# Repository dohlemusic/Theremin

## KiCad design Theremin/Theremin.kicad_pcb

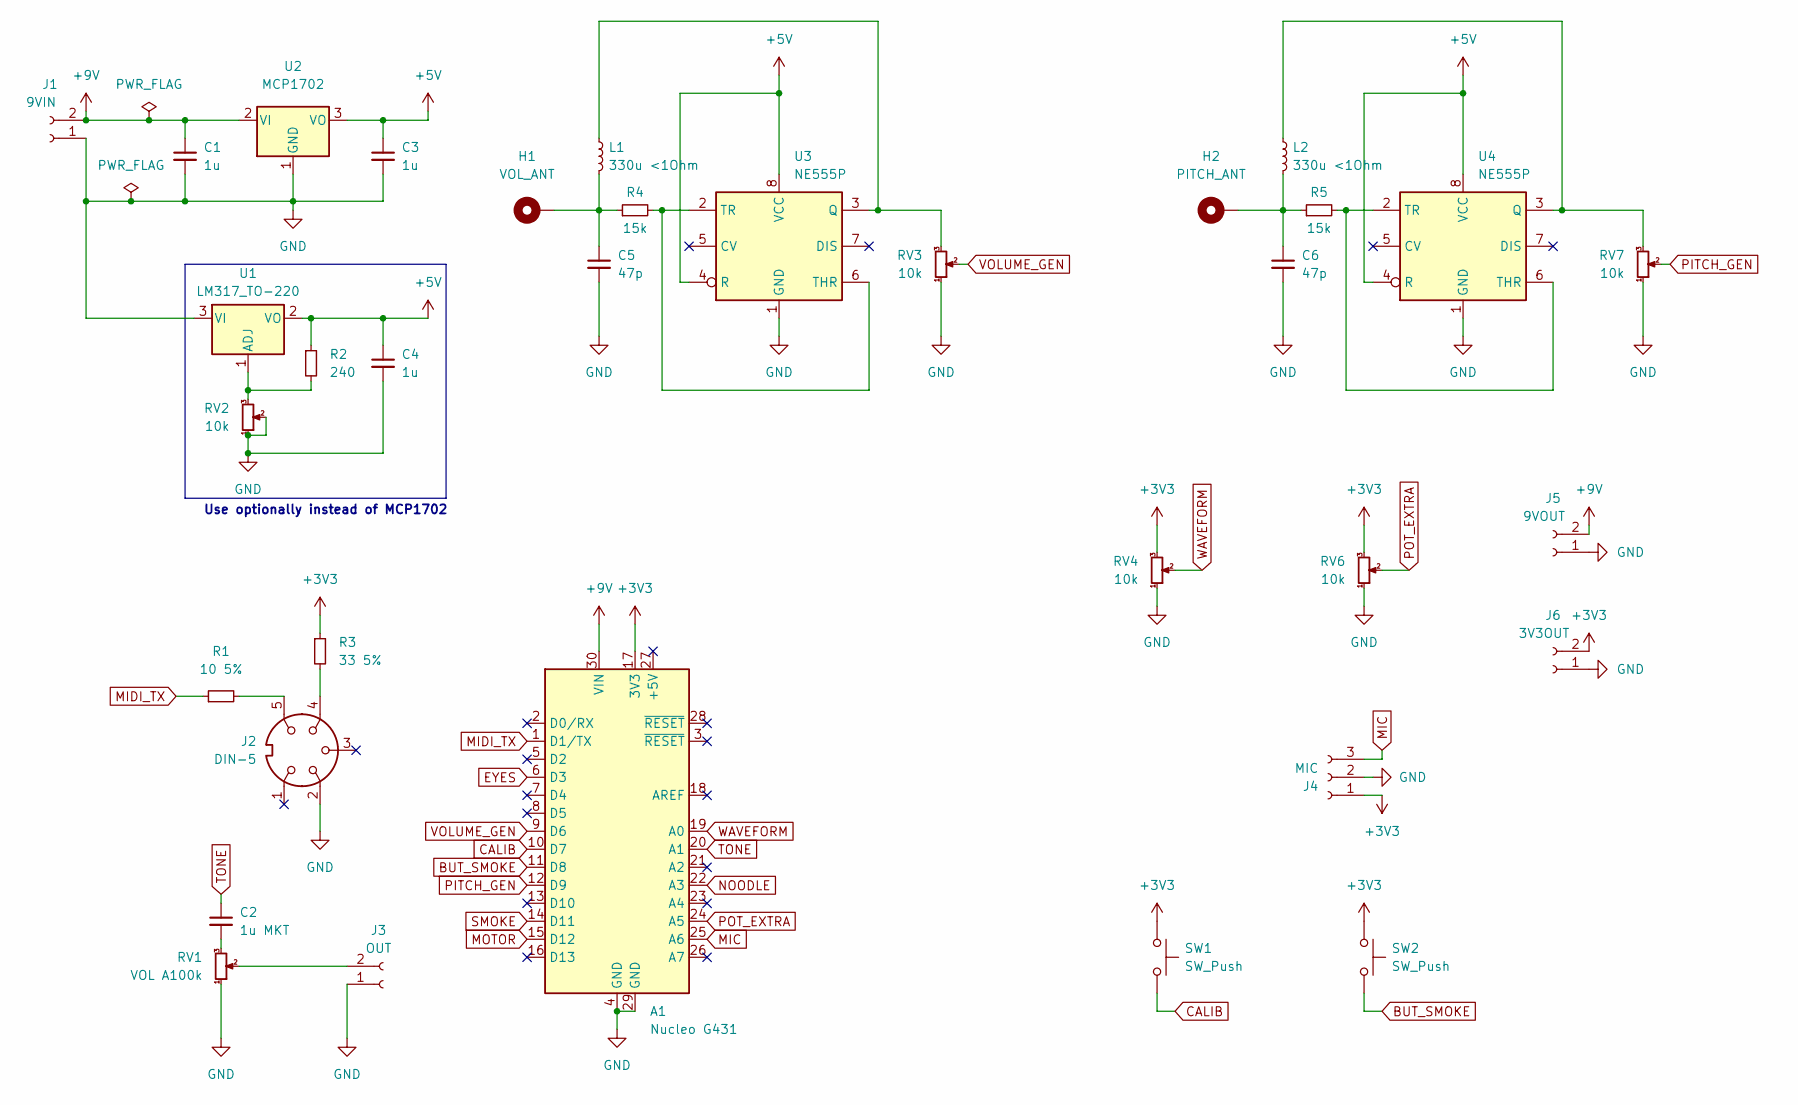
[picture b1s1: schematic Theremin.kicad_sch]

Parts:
A1: Nucleo G431; Arduino_Nano
C1, C3, C4: 1u; C_Rect_L7.0mm_W4.5mm_P5.00mm
C2: 1u MKT; C_Rect_L7.0mm_W4.5mm_P5.00mm
C5, C6: 47p; C_Disc_D3.0mm_W1.6mm_P2.50mm
H1: VOL_ANT; Pin_D1.0mm_L10.0mm
H2: PITCH_ANT; Pin_D1.0mm_L10.0mm
J1: 9VIN; JST_PH_B2B-PH-K_1x02_P2.00mm_Vertical
J2: DIN-5; MIDI_DIN5
J3: OUT; JST_PH_B2B-PH-K_1x02_P2.00mm_Vertical
J4: MIC; JST_PH_B3B-PH-K_1x03_P2.00mm_Vertical
J5: 9VOUT; JST_PH_B2B-PH-K_1x02_P2.00mm_Vertical
J6: 3V3OUT; JST_PH_B2B-PH-K_1x02_P2.00mm_Vertical
L1, L2: 330u <1Ohm; L_Radial_D7.5mm_P5.00mm_Fastron_07P
R1: 10 5%; R_Axial_DIN0207_L6.3mm_D2.5mm_P10.16mm_Horizontal
R2: 240; R_Axial_DIN0207_L6.3mm_D2.5mm_P10.16mm_Horizontal
R3: 33 5%; R_Axial_DIN0207_L6.3mm_D2.5mm_P10.16mm_Horizontal
R4, R5: 15k; R_Axial_DIN0207_L6.3mm_D2.5mm_P10.16mm_Horizontal
RV1: VOL A100k; JST_PH_B3B-PH-K_1x03_P2.00mm_Vertical
RV2, RV3, RV7: 10k; Potentiometer_Bourns_3299W_Vertical
RV4, RV6: 10k; JST_PH_B3B-PH-K_1x03_P2.00mm_Vertical
SW1, SW2: SW_Push; JST_PH_B2B-PH-K_1x02_P2.00mm_Vertical
U1: LM317_TO-220; TO-220-3_Vertical
U2: MCP1702; TO-92_Inline
U3, U4: NE555P; DIP-8_W7.62mm

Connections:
+3V3: A1.17 (3V3), J4.1, J6.2, R3.1, RV4.3, RV6.3, SW1.1, SW2.1
+5V: C3.1, C4.1, R2.1, U1.2 (VO), U2.3 (VO), U3.4 (R), U3.8 (VCC), U4.4 (R), U4.8 (VCC)
+9V: A1.30 (VIN), C1.1, J1.2, J5.2, U2.2 (VI)
BUT_SMOKE: A1.11 (D8), SW2.2
CALIB: A1.10 (D7), SW1.2
EYES: A1.6 (D3)
GND: A1.4 (GND), A1.29 (GND), C1.2, C3.2, C4.2, C5.2, C6.2, J1.1, J2.2, J3.1, J4.2, J5.1, J6.1, RV1.1, RV2.1, RV2.2, RV3.1, RV4.1, RV6.1, RV7.1, U1.3 (VI), U2.1 (GND), U3.1 (GND), U4.1 (GND)
MIC: A1.25 (A6), J4.3
MIDI_TX: A1.1 (D1/TX), R1.1
MOTOR: A1.15 (D12)
NOODLE: A1.22 (A3)
unnamed: C2.2, RV1.3
unnamed: C5.1, H1.1, L1.2, R4.1
unnamed: C6.1, H2.1, L2.2, R5.1
unnamed: J2.4, R3.2
unnamed: J2.5, R1.2
unnamed: J3.2, RV1.2
unnamed: L1.1, RV3.3, U3.3 (Q)
unnamed: L2.1, RV7.3, U4.3 (Q)
unnamed: R2.2, RV2.3, U1.1 (ADJ)
unnamed: R4.2, U3.2 (TR), U3.6 (THR)
unnamed: R5.2, U4.2 (TR), U4.6 (THR)
PITCH_GEN: A1.12 (D9), RV7.2
POT_EXTRA: A1.24 (A5), RV6.2
SMOKE: A1.14 (D11)
TONE: A1.20 (A1), C2.1
VOLUME_GEN: A1.9 (D6), RV3.2
WAVEFORM: A1.19 (A0), RV4.2

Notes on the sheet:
Use optionally instead of MCP1702

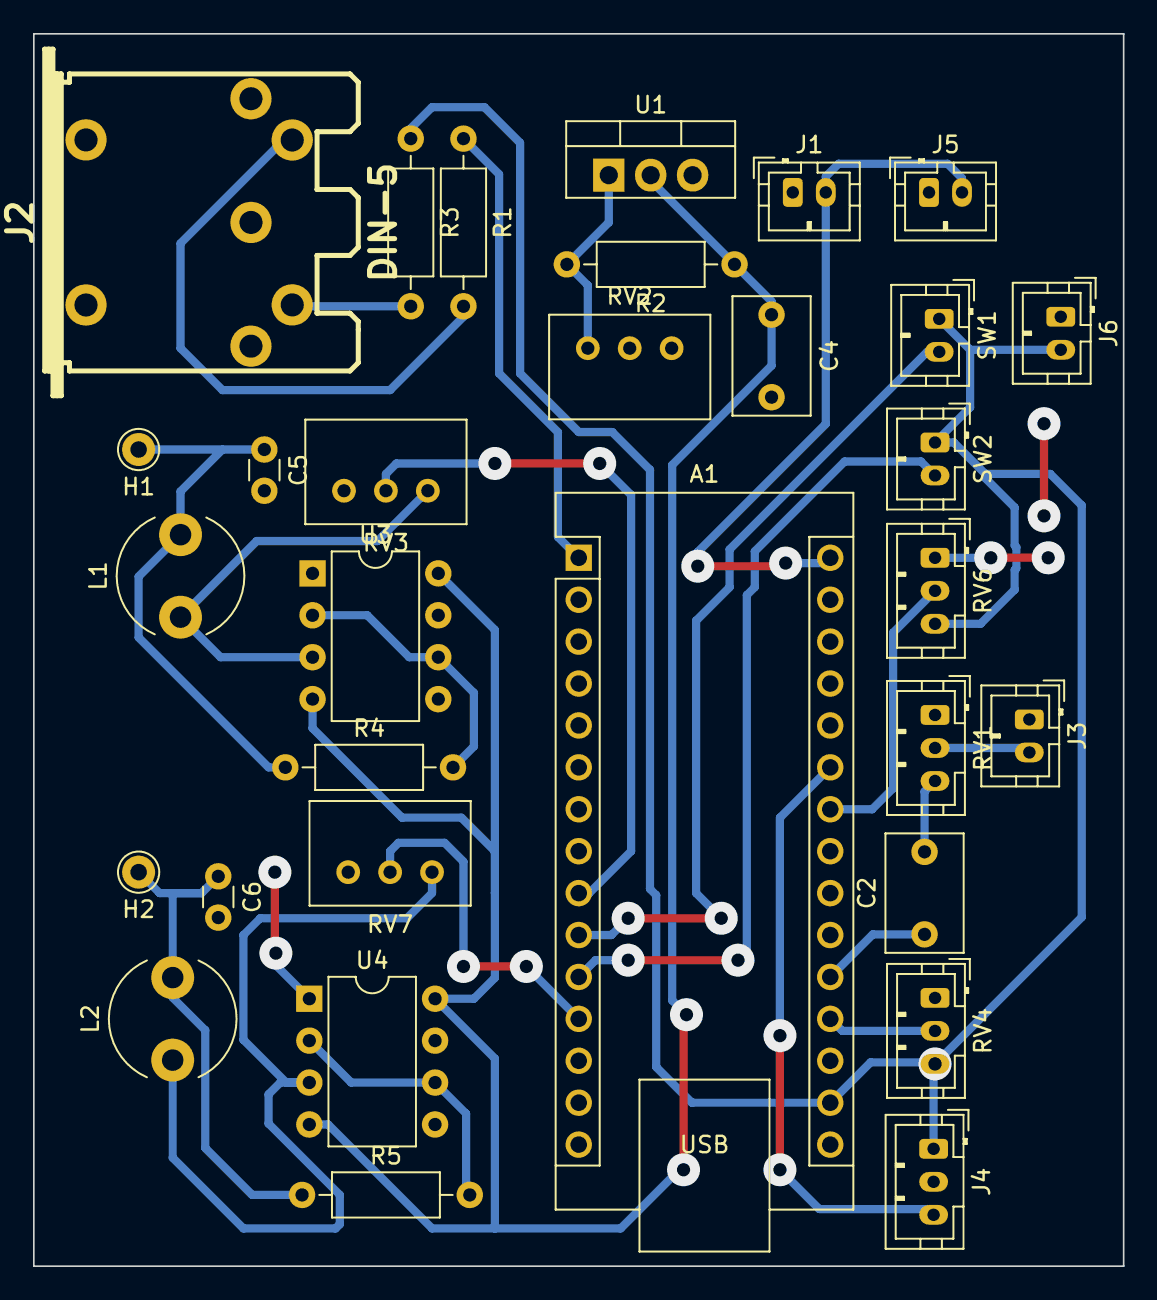
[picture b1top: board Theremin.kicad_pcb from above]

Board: 2 copper layers, 66.0 x 74.7 mm, 31 parts (0 on the bottom side), 24 nets.

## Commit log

2024-07-01 First revision with lots of bugs
2024-07-01 Separate voltage regulators for each oscillator and fix dac output
2024-07-03 Add source code
2024-07-03 Improve stability and playability
2024-07-05 Add ADC readout for tone setting
2024-07-06 Improve performance
2024-08-05 Fix ADC readouts and 1Hz pitch bug when away from antenna
2024-08-05 Add analog VCO draft
2024-10-19 Read potentiometers in main loop instead interrupt
